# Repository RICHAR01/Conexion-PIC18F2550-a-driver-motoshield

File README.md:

# Screenshot

# install dependencies
- Instalar Eagle

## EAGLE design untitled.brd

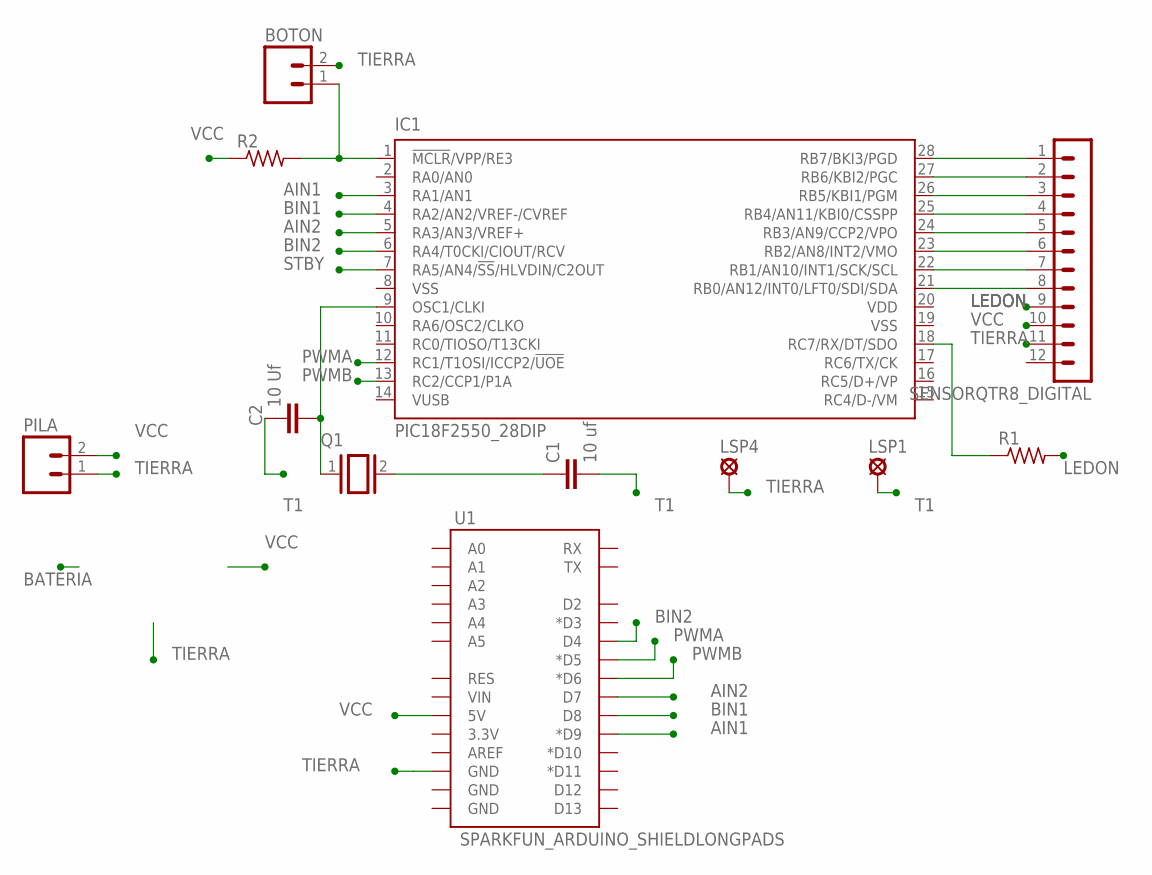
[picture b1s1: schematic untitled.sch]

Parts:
BOTON: MA02; 02PA
C1: 10 uf; C025-024X044
C2: 10 Uf; C025-024X044
IC1: PIC18F2550_28DIP; DIL28-3
LSP1, LSP4: LSP10
PILA: MA02; 02PA
Q1: XTAL/S; QS
R1, R2: R-US_0204/7; 0204/7
SENSORQTR8_DIGITAL: MA12-1
U1: SPARKFUN_ARDUINO_SHIELDLONGPADS; SPARKFUN_DUEMILANOVE_SHIELD_LONGPADS

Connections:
AIN1: IC1.3 (RA1/AN1), U1.D9 (*D9)
AIN2: IC1.5 (RA3/AN3/VREF+), U1.D7
BIN1: IC1.4 (RA2/AN2/VREF-/CVREF), U1.D8
BIN2: IC1.6 (RA4/T0CKI/CIOUT/RCV), U1.D4
LEDON: R1.2, SENSORQTR8_DIGITAL.9
unnamed: IC1.28 (RB7/BKI3/PGD), SENSORQTR8_DIGITAL.1
unnamed: IC1.27 (RB6/KBI2/PGC), SENSORQTR8_DIGITAL.2
unnamed: IC1.26 (RB5/KBI1/PGM), SENSORQTR8_DIGITAL.3
unnamed: IC1.25 (RB4/AN11/KBI0/CSSPP), SENSORQTR8_DIGITAL.4
unnamed: IC1.24 (RB3/AN9/CCP2/VPO), SENSORQTR8_DIGITAL.5
unnamed: IC1.23 (RB2/AN8/INT2/VMO), SENSORQTR8_DIGITAL.6
unnamed: IC1.22 (RB1/AN10/INT1/SCK/SCL), SENSORQTR8_DIGITAL.7
unnamed: IC1.21 (RB0/AN12/INT0/LFT0/SDI/SDA), SENSORQTR8_DIGITAL.8
unnamed: C2.2, IC1.9 (OSC1/CLKI), Q1.1
unnamed: C1.1, Q1.2
unnamed: IC1.18 (RC7/RX/DT/SDO), R1.1
unnamed: BOTON.1, IC1.1 (!MCLR!/VPP/RE3), R2.2
PWMA: IC1.12 (RC1/T1OSI/ICCP2/!UOE), U1.D5 (*D5)
PWMB: IC1.13 (RC2/CCP1/P1A), U1.D6 (*D6)
STBY: IC1.7 (RA5/AN4/!SS!/HLVDIN/C2OUT)
T1: C1.2, C2.1, LSP1.MP
TIERRA: BOTON.2, LSP4.MP, PILA.1, SENSORQTR8_DIGITAL.11, U1.GND@2 (GND)
VCC: PILA.2, R2.1, SENSORQTR8_DIGITAL.10, U1.5V
VDD: IC1.20 (VDD)
VSS: IC1.8 (VSS), IC1.19 (VSS)

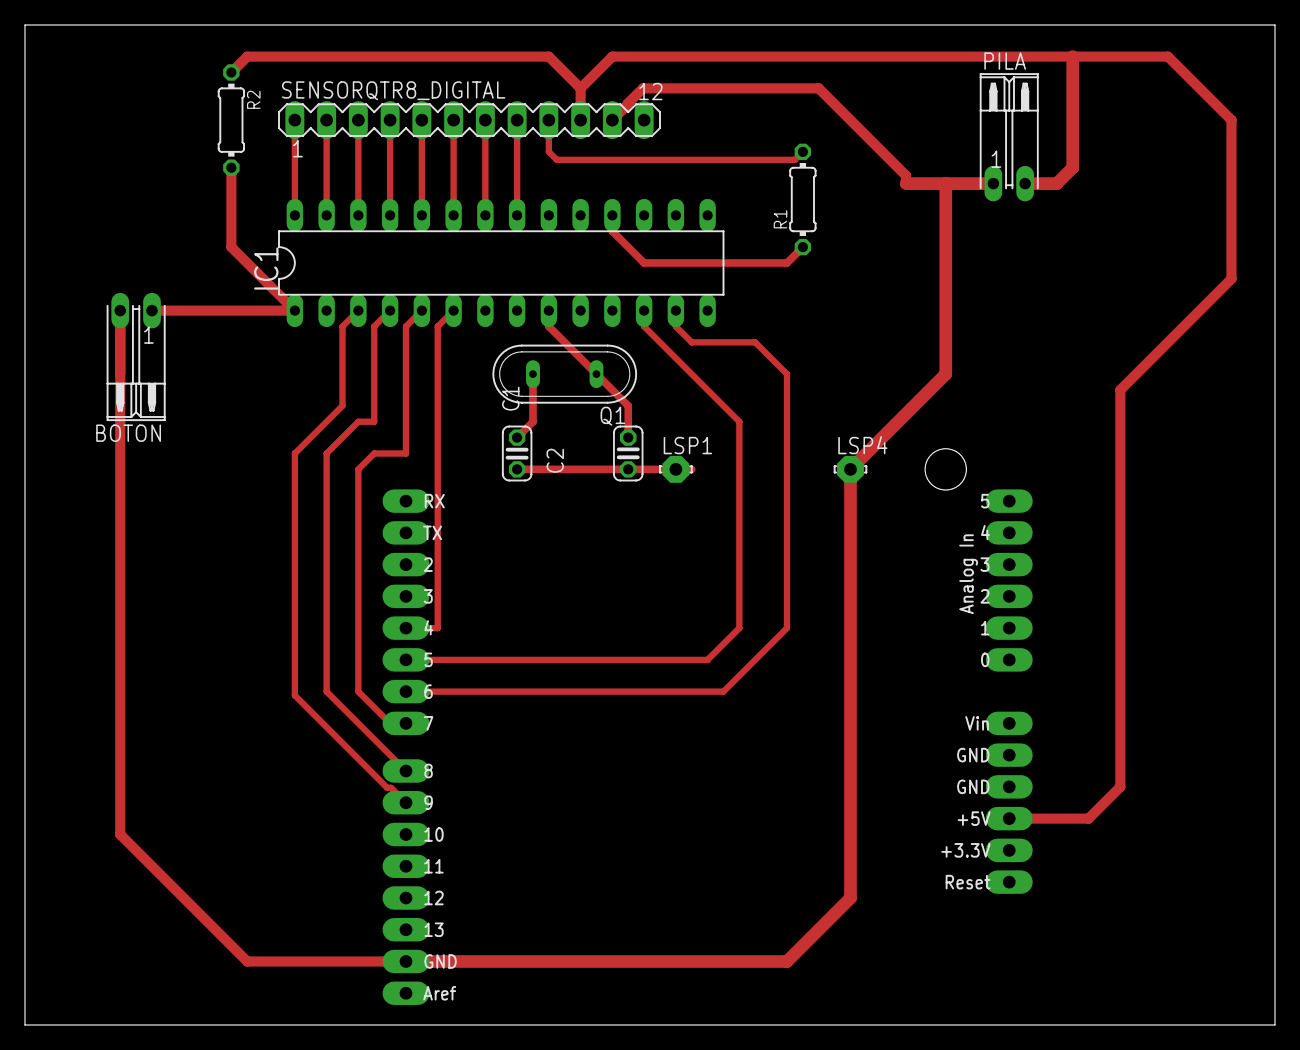
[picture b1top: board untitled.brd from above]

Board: 2 copper layers, 100.0 x 80.0 mm, 12 parts (0 on the bottom side), 23 nets.
